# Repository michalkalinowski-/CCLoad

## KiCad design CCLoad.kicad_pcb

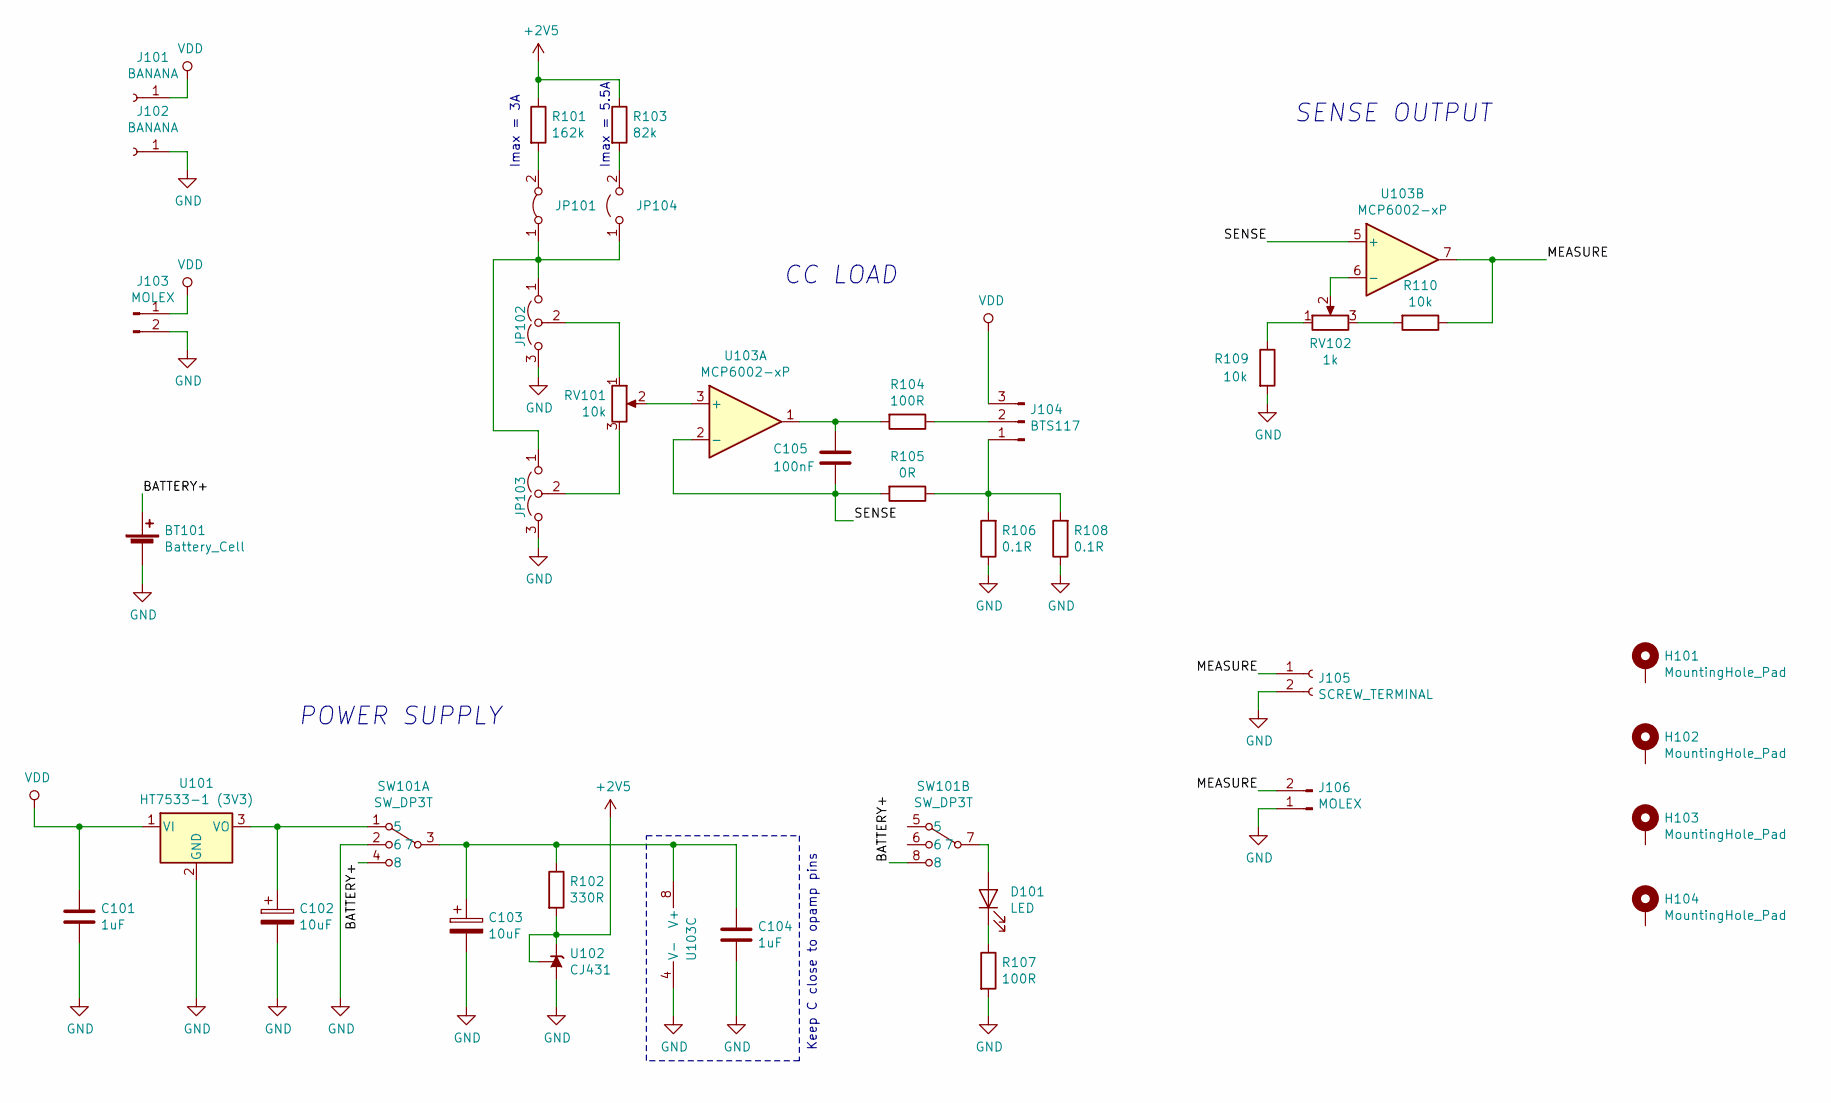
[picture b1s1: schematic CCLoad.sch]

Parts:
BT101: Battery_Cell; BatteryHolder_Keystone_1060_1x2032
C101, C104: 1uF; C_0805_2012Metric_Pad1.15x1.40mm_HandSolder
C102, C103: 10uF; CP_EIA-3216-12_Kemet-S_Pad1.58x1.35mm_HandSolder; LCSC C7171
C105: 100nF; C_0805_2012Metric_Pad1.15x1.40mm_HandSolder
D101: LED; LED_0805_2012Metric_Pad1.15x1.40mm_HandSolder
H101, H102, H103, H104: MountingHole_Pad; MountingHole_3.7mm_Pad
J101, J102: BANANA; Binding_Post_Caltest_CT2234
J103, J106: MOLEX; PinHeader_1x02_P2.54mm_Vertical
J104: BTS117; BTS117_outboard
J105: SCREW_TERMINAL; Molex_KK-254_AE-6410-02A_1x02_P2.54mm_Vertical
JP101: Jumper_2_Bridged; SolderJumper-2_P1.3mm_Bridged_RoundedPad1.0x1.5mm
JP102, JP103: Jumper_3_Open; SolderJumper-3_P1.3mm_Bridged12_RoundedPad1.0x1.5mm
JP104: Jumper_2_Open; SolderJumper-2_P1.3mm_Open_RoundedPad1.0x1.5mm
R101: 162k; R_0805_2012Metric_Pad1.15x1.40mm_HandSolder
R102: 330R; R_0805_2012Metric_Pad1.15x1.40mm_HandSolder; LCSC C17630
R103: 82k; R_0805_2012Metric_Pad1.15x1.40mm_HandSolder; LCSC C17840
R104, R107: 100R; R_0805_2012Metric_Pad1.15x1.40mm_HandSolder
R105: 0R; R_0805_2012Metric_Pad1.15x1.40mm_HandSolder
R106, R108: 0.1R; R_2512_6332Metric_Pad1.52x3.35mm_HandSolder; LCSC C63324
R109, R110: 10k; R_0805_2012Metric_Pad1.15x1.40mm_HandSolder
RV101: 10k; Potentiometer_Alps_RK09K_Single_Vertical; LCSC C361173
RV102: 1k; Potentiometer_Bourns_3314J_Vertical; LCSC C124640
SW101: SW_DP3T; SW_DP3T_ALPS_SSSS223600
U101: HT7533-1 (3V3); SOT-89-3_Handsoldering; LCSC C14289
U102: CJ431; SOT-23; LCSC C3113
U103: MCP6002-xP; SOIC-8_3.9x4.9mm_P1.27mm

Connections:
+2V5: R101.1, R102.2, R103.1, U102.1 (REF), U102.2 (K)
/BATTERY+: BT101.1 (+), SW101.4 (8), SW101.8
/MEASURE: J105.1, J106.2, R110.1, U103.7
/SENSE: C105.2, R105.2, U103.2 (-), U103.5 (+)
GND: BT101.2 (-), C101.2, C102.2, C103.2, C104.2, J102.1, J103.2, J105.2, J106.1, JP102.3 (B), JP103.3 (B), R106.1, R107.2, R108.1, R109.2, SW101.2 (6), U101.2 (GND), U102.3 (A), U103.4 (V-)
unnamed: C102.1, SW101.1 (5), U101.3 (VO)
unnamed: C103.1, C104.1, R102.1, SW101.3 (7), U103.8 (V+)
unnamed: C105.1, R104.2, U103.1
unnamed: D101.1 (K), R107.1
unnamed: D101.2 (A), SW101.7
unnamed: J104.1, R105.1, R106.2, R108.2
unnamed: J104.2, R104.1
unnamed: JP101.1 (A), JP102.1 (A), JP103.1 (A), JP104.1 (A)
unnamed: JP101.2 (B), R101.2
unnamed: JP102.2 (C), RV101.1
unnamed: JP103.2 (C), RV101.3
unnamed: JP104.2 (B), R103.2
unnamed: R109.1, RV102.1
unnamed: R110.2, RV102.3
unnamed: RV101.2, U103.3 (+)
unnamed: RV102.2, U103.6 (-)
VDD: C101.1, J101.1, J103.1, J104.3, U101.1 (VI)

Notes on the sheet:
POWER SUPPLY
CC LOAD
SENSE OUTPUT
Keep C close to opamp pins
Imax = 3A
Imax = 5.5A

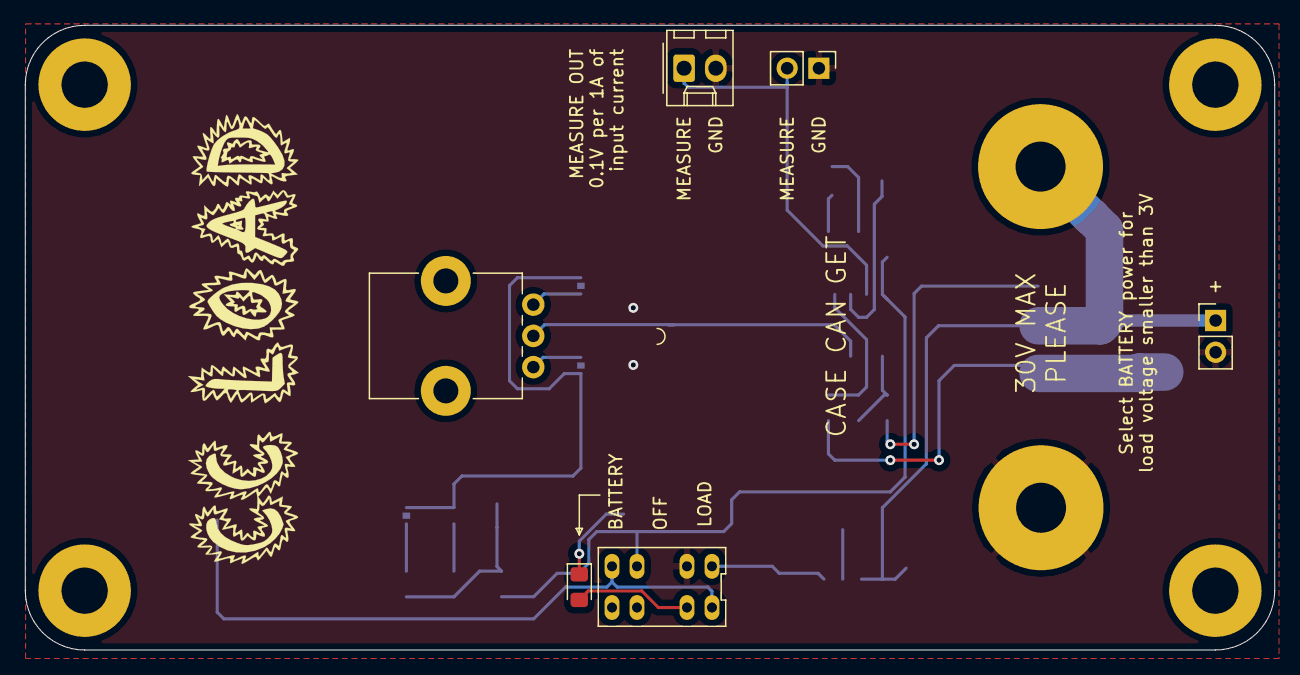
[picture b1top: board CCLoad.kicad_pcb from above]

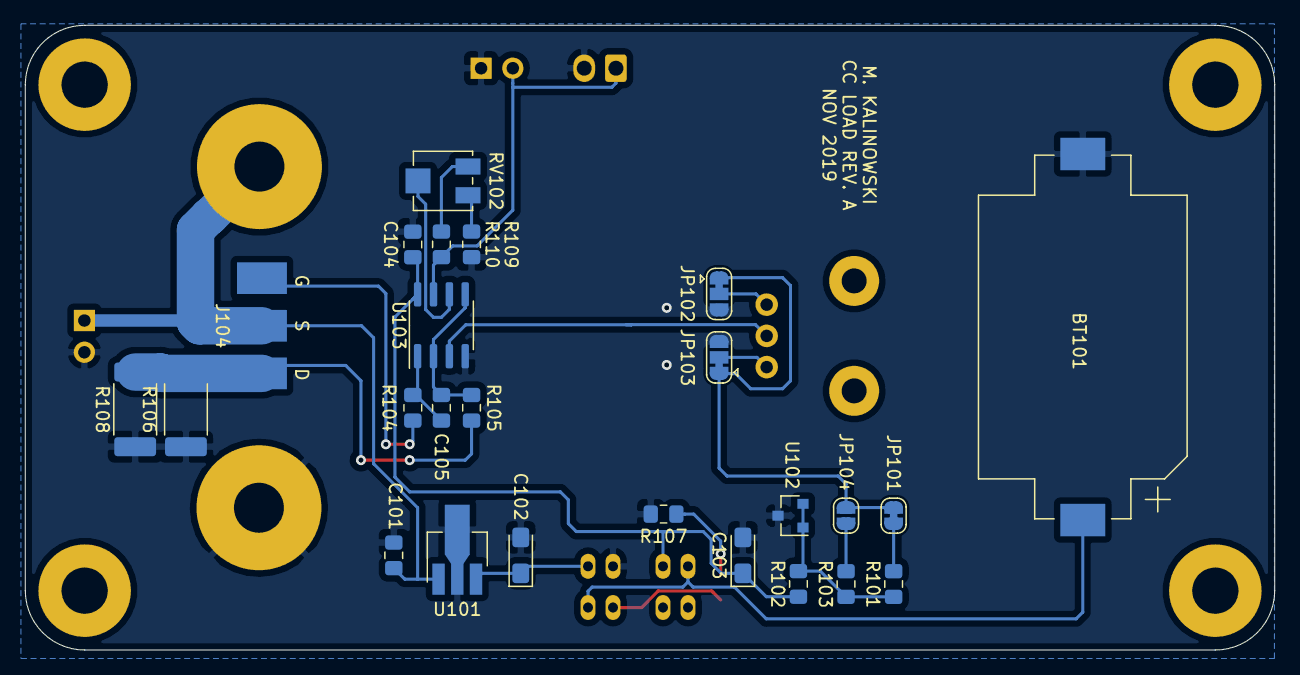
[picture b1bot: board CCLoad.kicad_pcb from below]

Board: 2 copper layers, 100.0 x 50.0 mm, 37 parts (25 on the bottom side), 22 nets.

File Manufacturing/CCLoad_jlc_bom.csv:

"Source:","/Users/michalka/Developer/electronics/CCLoad/CCLoad.sch"
"Date:","2019 November 26, Tuesday 13:17:44"

"Component Count:","36"

"Comment","Designator","Footprint","LCSC Part #"
"Battery_Cell:Battery_Cell:Battery:BatteryHolder_Keystone_1060_1x2032","BT101","SMD-BAT-CR2032-BS-6-1","C70377"
"C:1uF:Capacitor_SMD:C_0805_2012Metric_Pad1.15x1.40mm_HandSolder","C101, C104","0805","C28323"
"CP:10uF:Capacitor_Tantalum_SMD:CP_EIA-3216-12_Kemet-S_Pad1.58x1.35mm_HandSolder","C102, C103","CASE-A_3216","C7171"
"C:100nF:Capacitor_SMD:C_0805_2012Metric_Pad1.15x1.40mm_HandSolder","C105","0805","C49678"
"LED:LED:LED_SMD:LED_0805_2012Metric_Pad1.15x1.40mm_HandSolder","D101","LED_0805","C84256"
"Conn_01x01_Female:BANANA:CCLoad:Binding_Post_Caltest_CT2234","J101, J102","",""
"Conn_01x02_Male:MOLEX:Connector_PinHeader_2.54mm:PinHeader_1x02_P2.54mm_Vertical","J103, J106","",""
"Conn_01x03_Male:BTS117:CCLoad:BTS117_outboard","J104","",""
"Conn_01x02_Female:SCREW_TERMINAL:Connector_Molex:Molex_KK-254_AE-6410-02A_1x02_P2.54mm_Vertical","J105","",""
"R:162k:Resistor_SMD:R_0805_2012Metric_Pad1.15x1.40mm_HandSolder","R101","0805",""
"R:330R:Resistor_SMD:R_0805_2012Metric_Pad1.15x1.40mm_HandSolder","R102","0805","C17630"
"R:82k:Resistor_SMD:R_0805_2012Metric_Pad1.15x1.40mm_HandSolder","R103","0805","C17840"
"R:100R:Resistor_SMD:R_0805_2012Metric_Pad1.15x1.40mm_HandSolder","R104, R107","0805","C17408"
"R:0R:Resistor_SMD:R_0805_2012Metric_Pad1.15x1.40mm_HandSolder","R105","0805","C17477"
"R:0.05R:Resistor_SMD:R_2512_6332Metric_Pad1.52x3.35mm_HandSolder","R106","",""
"R:10k:Resistor_SMD:R_0805_2012Metric_Pad1.15x1.40mm_HandSolder","R108, R109","0805",""
"R_POT:10k:Potentiometer_THT:Potentiometer_Alps_RK09K_Single_Vertical","RV101","",""
"R_POT:1k:Potentiometer_SMD:Potentiometer_Bourns_3314J_Vertical","RV102","",""
"SW_DP3T:SW_DP3T:CCLoad:SW_DP3T_ALPS_SSSS223600","SW101","",""
"LM2936-3.0:HT7533-1 (3V3):Package_TO_SOT_SMD:SOT-89-3_Handsoldering","U101","",""
"TL432DBZ:CJ431:Package_TO_SOT_SMD:SOT-23","U102","",""
"MCP6002-xP:MCP6002-xP:Package_SO:SOIC-8_3.9x4.9mm_P1.27mm","U103","",""

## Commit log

2020-01-22 finished board, generated output files
2020-01-22 fixes references
2020-01-22 updates banana jack footprints
2020-02-04 increases banana mounting hole to 4.5mm
